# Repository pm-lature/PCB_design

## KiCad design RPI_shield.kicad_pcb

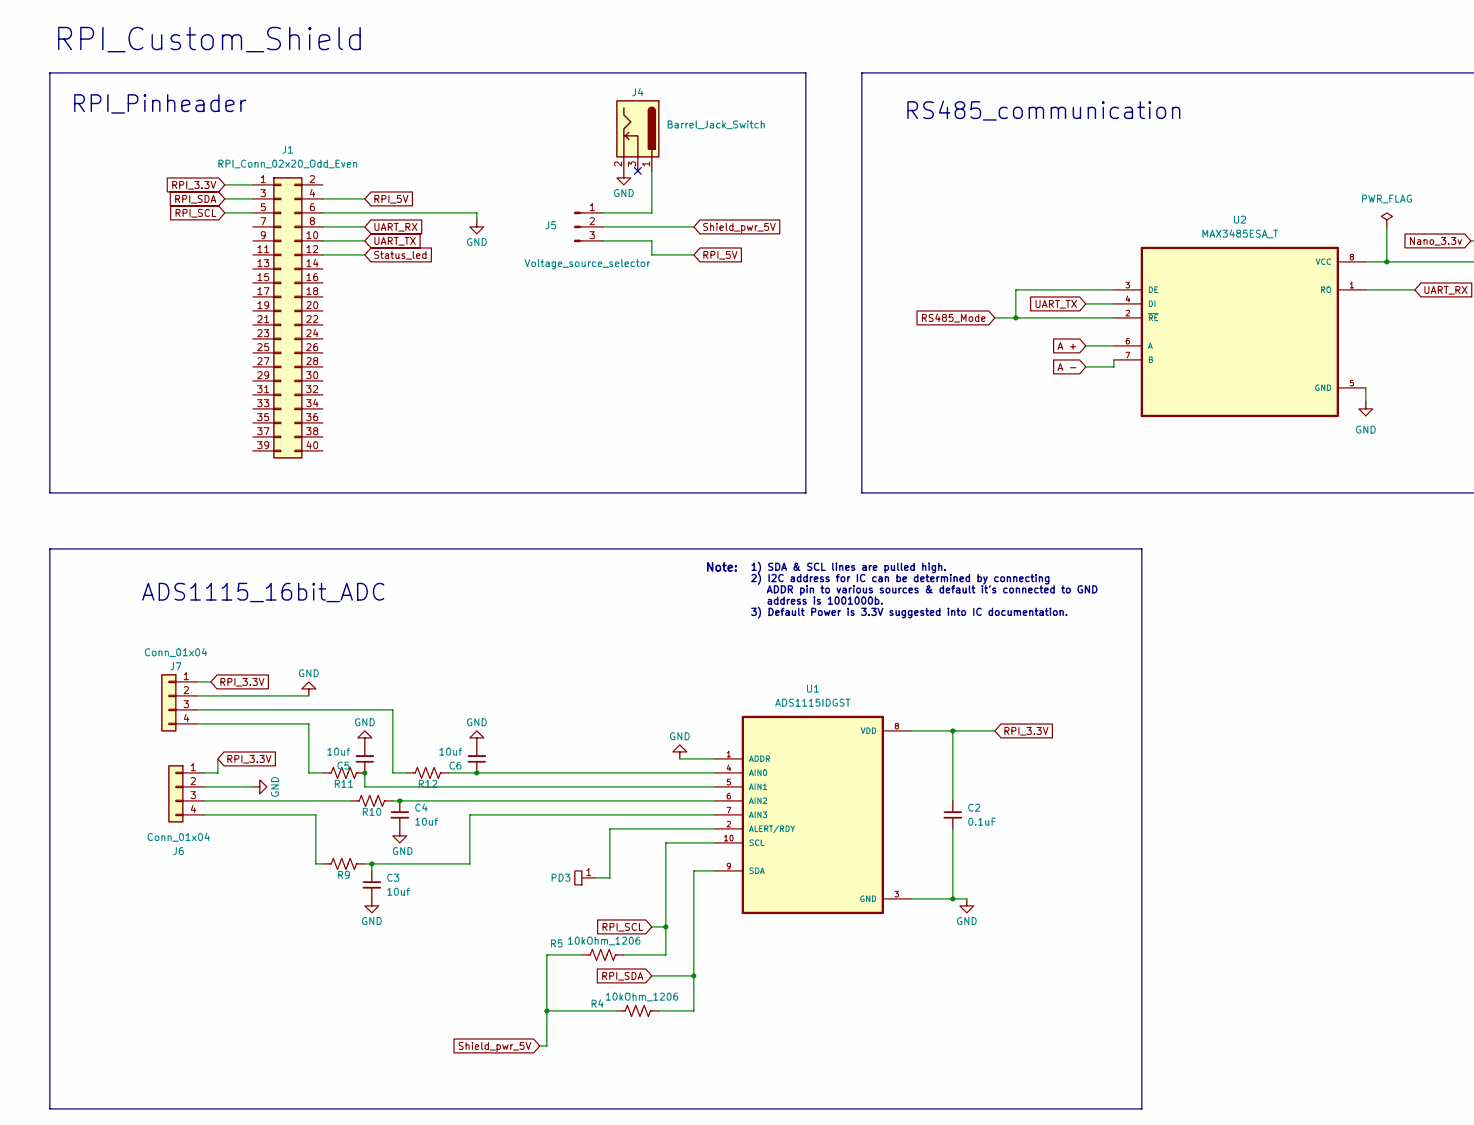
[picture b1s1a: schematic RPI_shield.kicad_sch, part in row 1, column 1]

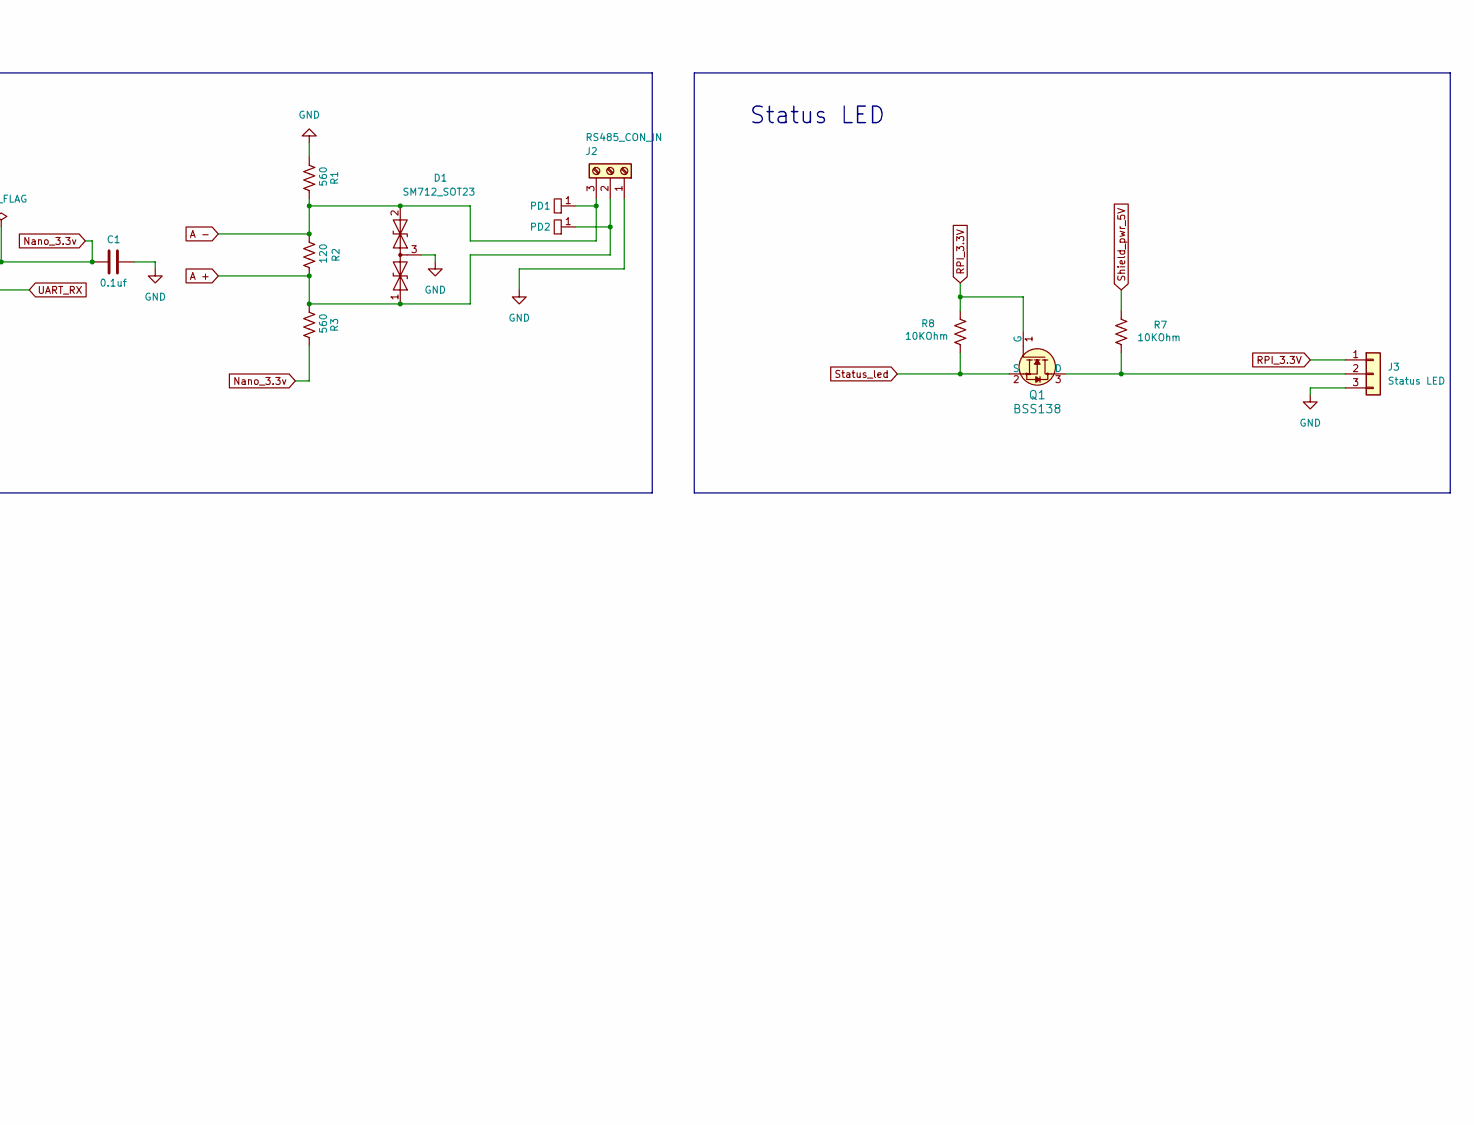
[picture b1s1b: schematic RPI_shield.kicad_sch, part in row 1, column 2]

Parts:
C1: 0.1uf; C_0805_2012Metric_Pad1.18x1.45mm_HandSolder
C2: 0.1uF; C_0805_2012Metric_Pad1.18x1.45mm_HandSolder
C3, C4, C5, C6: 10uf; C_0805_2012Metric_Pad1.18x1.45mm_HandSolder
D1: SM712_SOT23; SOT-23
J1: RPI_Conn_02x20_Odd_Even; PinSocket_2x20_P2.54mm_Vertical
J2: RS485_CON_IN; TerminalBlock_Phoenix_MKDS-1,5-3-5.08_1x03_P5.08mm_Horizont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
J3: Status LED; JST_XH_B3B-XH-A_1x03_P2.50mm_Vertical
J4: Barrel_Jack_Switch; BarrelJack_Horizontal
J5: Voltage_source_selector; PinHeader_1x03_P2.54mm_Vertical
J6, J7: Conn_01x04; JST_XH_B4B-XH-A_1x04_P2.50mm_Vertical
PD1, PD2, PD3: pad_2x2mm
Q1: BSS138; SOT-23-3; MPN BSS138
R1, R3: 560; R_0805_2012Metric_Pad1.20x1.40mm_HandSolder
R2: 120; R_0805_2012Metric_Pad1.20x1.40mm_HandSolder
R4, R5, R9, R10, R11, R12: 10kOhm_1206; R_0805_2012Metric_Pad1.20x1.40mm_HandSolder
R7, R8: 10KOhm; R_0805_2012Metric_Pad1.20x1.40mm_HandSolder
U1: ADS1115IDGST; SOP50P490X110-10N
U2: MAX3485ESA_T; SOIC127P600X175-8N

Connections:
A +: D1.1 (A1), J2.2, PD2.1, R2.1, R3.2, U2.6 (A)
A -: D1.2 (A2), J2.3, PD1.1, R1.1, R2.2, U2.7 (B)
GND: C1.1, C2.2, C3.2, C4.2, C5.2, C6.2, D1.3 (common), J1.6, J2.1, J3.3, J4.2, J6.2, J7.2, R1.2, U1.1 (ADDR), U1.3 (GND), U2.5 (GND)
Nano_3.3v: C1.2, R3.1, U2.8 (VCC)
unnamed: J3.2, Q1.3 (D), R7.1
unnamed: J4.1, J5.1
unnamed: J6.3, R10.1
unnamed: J6.4, R9.1
unnamed: J7.3, R12.1
unnamed: J7.4, R11.1
unnamed: C6.1, R12.2, U1.4 (AIN0)
unnamed: C5.1, R11.2, U1.5 (AIN1)
unnamed: C4.1, R10.2, U1.6 (AIN2)
unnamed: C3.1, R9.2, U1.7 (AIN3)
unnamed: PD3.1, U1.2 (ALERT/RDY)
RPI_3.3V: C2.1, J1.1, J3.1, J6.1, J7.1, Q1.1 (G), R8.2, U1.8 (VDD)
RPI_5V: J1.4, J5.3
RPI_SCL: J1.5, R5.2, U1.10 (SCL)
RPI_SDA: J1.3, R4.2, U1.9 (SDA)
RS485_Mode: U2.2 (~RE), U2.3 (DE)
Shield_pwr_5V: J5.2, R4.1, R5.1, R7.2
Status_led: J1.12, Q1.2 (S), R8.1
UART_RX: J1.8, U2.1 (RO)
UART_TX: J1.10, U2.4 (DI)

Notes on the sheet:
RPI_Pinheader
1) SDA & SCL lines are pulled high. 2) I2C address for IC can be determined by connecting ADDR pin to various sources & default it's connected to GND address is 1001000b. 3) Default Power is 3.3V suggested into IC documentation.
ADS1115_16bit_ADC
RPI_Custom_Shield
Status LED
Note:
RS485_communication

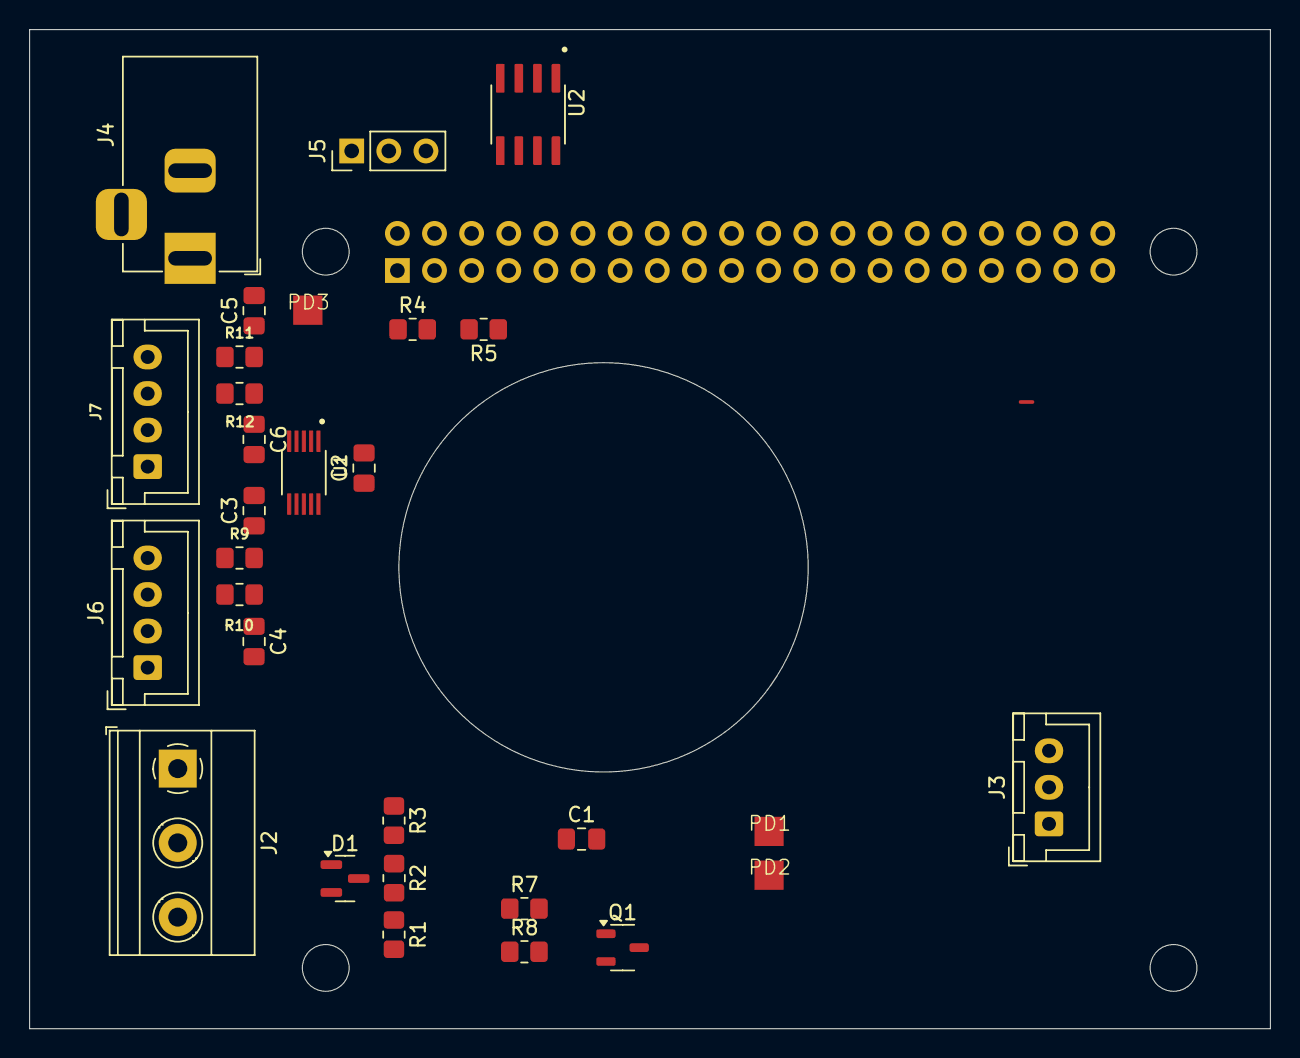
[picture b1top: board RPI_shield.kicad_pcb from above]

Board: 2 copper layers, 84.9 x 68.3 mm, 31 parts (1 on the bottom side), 24 nets.

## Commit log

2025-05-13 intialize commit
2025-05-13 sdfsdff
